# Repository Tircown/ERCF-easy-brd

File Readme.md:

# ERCF EASY BRD

**Be careful not to invert polarity in the screw terminal or it may damage the board and even more.**

**Do not use the servo connector as an input or do it at your own risk.\
Voltage input connected to general I/O pins may cause chip damage if it' higher than 3.3V .**

## BOM
Component | Position
------------ | -------------
Resistor 10K | R1, R2, R3, R4
Capacitor ceramic 0.33uF 25V | C1
Capacitor ceramic 0.1uF 25V | C2
Capacitor 100uF 25V | C3, C4
2P Screw terminal P=5.08 | J5
3P JST-XH male P=2.54 | J1, J2, J3, J4
4P JST-XH male P=2.54 | J6, J7
8P Header socket P=2.54 | *4x for U4 and U3*
2P Header socket P=2.54 | *1x for U4*
5P Header pin P=2.54 | J6
7P Header socket female P=2.54 | *(optionnal) 2x for Seeeduino XIAO*
Seeeduino XIAO or Adafruit QT Py (same footprint & pinout)| U1
Voltage regulator L7805CV | U2
SilentStepStick TMC2209 | U3, U4
Jumper P=2.54 | *2x for J6*
Heatsink for TO-220 | *(recommended) 1x for the L7805CP (1)*

*(1) You will need to bend a fin and remove the pin of the TO-220 heatsink. Make sure the PCB has no bare traces underneath or apply an insolator before (i.e. piece of chattertone).*

## Configure the MCU - Seeeduino XIAO
* Install bossac (version ≥1.8)
```
sudo apt install libreadline-dev libwxgtk3.0-*
git clone https://github.com/shumatech/BOSSA.git
cd BOSSA
make
sudo cp bin/bossac /usr/local/bin
```
* Prepare the firmware
```
cd ~/klipper
make menuconfig
```

```
make clean
make
```
* Flashing the Seeeduino XIAO
Connect the Seeeduino XIAO to your raspberry if it's not already done.
Get the port of the XIAO, i.e. `ls /dev/tty*`, and modify the default `/dev/ttyACM1` in the command line bellow.
Use tweezers or short lines to short the RST pins in the diagram twice. The orange LED lights flicker on and light up. Then send in the next few seconds this command line matching your port.
```
sudo /usr/local/bin/bossac -i -d -p /dev/ttyACM1 -e -w -v -R --offset=0x2000 out/klipper.bin
```

More informations on how to reset for flashing:\
https://wiki.seeedstudio.com/Seeeduino-XIAO/#enter-bootloader-mode

## Klipper configuration
See [ercf_hardware.cfg](config/Seeeduino%20XIAO%20-%20SAMD21G18/ercf_hardware.cfg) for the Seeeduino XIAO (most common solution)
Other microcontrollers configurations are available in config/

## Get the PCB Board
If you want to support my work: https://www.pcbway.com/project/shareproject/ERCF_EASY_BRD.html \
*note: default setting is "HASL lead free" but if it doesn't matter to you, just change this option to get more affordable boards.*

Or just download the Gerber files and upload it to the manufacturer of your choice.

## Dimensions

## More pictures

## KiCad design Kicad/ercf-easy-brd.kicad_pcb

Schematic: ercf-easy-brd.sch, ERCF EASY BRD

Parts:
C1: 0.33uF; C_Disc_D3.0mm_W1.6mm_P2.50mm
C2: 0.1uF; C_Disc_D3.0mm_W1.6mm_P2.50mm
C3, C4: 100uF; CP_Radial_D8.0mm_P3.50mm
H1, H2, H3: MountingHole; MountingHole_3.2mm_M3
J1, J2, J3, J4: Conn_01x03_Male; JST_XH_B3B-XH-A_1x03_P2.50mm_Vertical
J5: Screw_Terminal_01x02; TerminalBlock_bornier-2_P5.08mm_2
J6: Conn_01x05_Male; PinHeader_1x05_P2.54mm_Vertical_2
J7, J8: Conn_01x04_Male; JST_XH_B4B-XH-A_1x04_P2.50mm_Vertical
JP7, JP9: Jumper_NO_Small; SolderJumper-2_P1.3mm_Open_RoundedPad1.0x1.5mm
JP8, JP10: Jumper_NC_Small; SolderJumper-2_P1.3mm_Bridged_RoundedPad1.0x1.5mm
R1, R2, R3, R4: 10k; R_Axial_DIN0207_L6.3mm_D2.5mm_P7.62mm_Horizontal
U1: SeeeduinoXIAO; SeeeduinoXIAO-MODULE14P
U2: L7805; TO-220-3_Vertical
U3, U4: TMC2209_SILENTSTEPSTICK; MODULE_TMC2209_SILENTSTEPSTICK; PARTREV v11

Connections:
+3V3: J2.3, J3.3, J4.3, R3.2, R4.2, U1.12, U3.JP2_7, U4.JP1_7, U4.JP2_7
+5V: C2.1, J1.3, U2.3 (OUT)
ENCODER: J2.1, U1.11
EXTRA: J6.2, U1.9
G-DIR: U1.3, U3.JP1_1
G-EN: R3.1, U1.1, U3.JP1_8
G-STEP: U1.2, U3.JP1_2
GND: C1.2, C2.2, C3.2, C4.2, J1.2, J2.2, J3.2, J4.2, J5.1, R1.2, R2.2, U1.13, U2.2 (GND), U3.JP1_6, U3.JP1_7, U3.JP2_2, U3.JP2_8, U4.JP1_6, U4.JP2_2, U4.JP2_8
unnamed: J3.1, J6.1
unnamed: J4.1, J6.5
unnamed: J6.3, U4.JP4_1
unnamed: J7.1, U3.JP2_5
unnamed: J7.2, U3.JP2_4
unnamed: J7.3, U3.JP2_3
unnamed: J7.4, U3.JP2_6
unnamed: J8.1, U4.JP2_5
unnamed: J8.2, U4.JP2_4
unnamed: J8.3, U4.JP2_3
unnamed: J8.4, U4.JP2_6
unnamed: JP7.1, U3.JP1_4
unnamed: JP8.2, U3.JP1_5
unnamed: JP9.1, U4.JP1_4
unnamed: JP10.2, U4.JP1_5
unnamed: R1.1, U3.JP1_3
unnamed: R2.1, U4.JP1_3
S-DIR: U1.7, U4.JP1_1
S-EN: R4.1, U1.4, U4.JP1_8
S-MIN: J6.4, U1.8
S-STEP: U1.6, U4.JP1_2
SERVO: J1.1, U1.10
UART: JP7.2, JP8.1, JP9.2, JP10.1, U1.5
VDC: C1.1, C3.1, C4.1, J5.2, U2.1 (IN), U3.JP2_1, U4.JP2_1

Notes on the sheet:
DCDC-5V
GEAR STEPPER
SELECTOR STEPPER
ENDSTOPS
MCU
- ENCODER
- SERVO
- EXTRA (TOOLHEAD)
- SELECTOR ENDSTOP
CASE 1 (typical): 1-2 PA7 = Extra Endstop 4-5 PB9 = Selector Endstop CASE 2 : 1-2 PA7 = Extra Endstop 3-4 PB9 = Selector TMC2209 Stallguard CASE 3 : 2-3 PA7 = Selector TMC2209 Stallguard 4-5 PB9 = Selector Endstop
stallguard

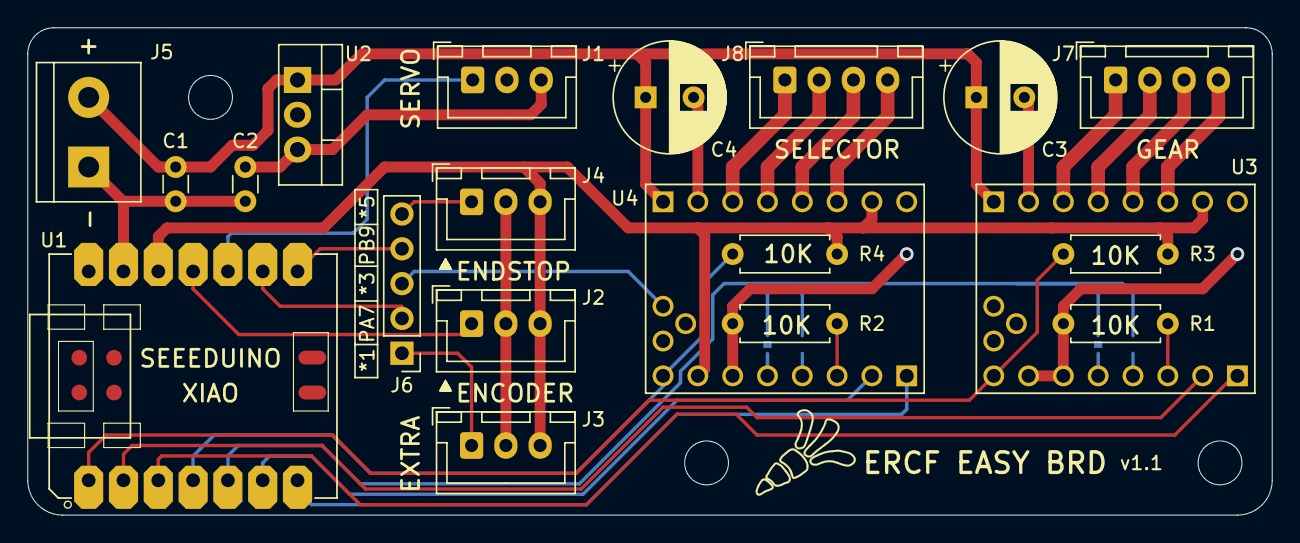
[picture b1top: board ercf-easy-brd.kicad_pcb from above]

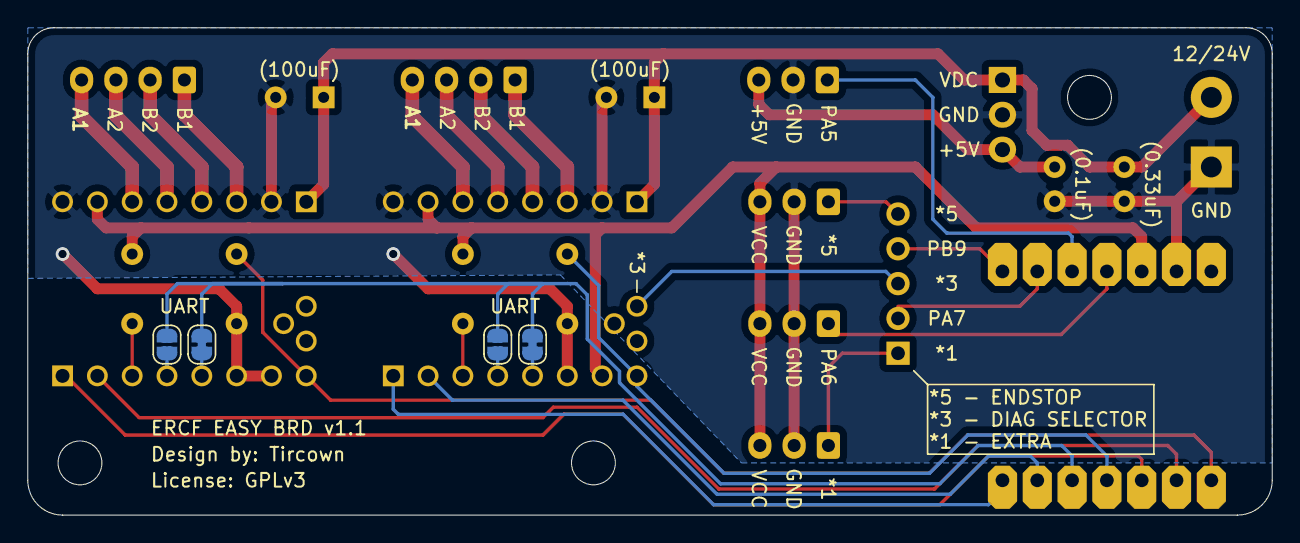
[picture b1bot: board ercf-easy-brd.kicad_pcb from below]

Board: 2 copper layers, 90.8 x 35.6 mm, 27 parts (4 on the bottom side), 32 nets.

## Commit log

2021-05-31 initial
2021-05-31 Fix readme
    Fix readme
2021-05-31 Fix comment on schematic and layout
    Fix comment on schematic and layout
2021-05-31 Add step file
    Add step file
2021-05-31 Fix typo
    Fix typo
2021-05-31 Fix XIAO footprint
    Fix XIAO footprint: one hole smaller
    Rename folder to Kicad
2021-06-01 Complete config sample
    Add the multi mcu section
    Edit pins accordingly to the mcu
    Fix the servo pin
2021-06-01 Open 2nd jumper
    Open the jumper for the second UART pin
2021-06-01 Fix accidently remove the logo
    Fix accidentally remove the logo
    Minor typo in readme
2021-06-17 Fix pin in config
    Fix endstop pin and gear_stepper enable pin in config sample
2021-06-18 PCB v1.1
    PCB v1.1:
    - VCC for endstop, encoder and extra are now 3V3
    - Fix gear stepper ground plane was not connected to GND
    - Improve the tracks width for power and motors
2021-06-24 Rename project
    Rename project from ercf-ez-board to ercf-easy-brd to avoid confusion: it is not a TH3D product.
2021-06-24 Add Adafruit QT Py and general warnings
    Add Adafruit QT Py to the list of mcu since it can be used as a direct replacement.
    Add warnings for the wiring
2021-06-24 Add PCBWay project link
    Add PCBWay project link
2021-06-26 Mod: bracket bottom
    Bottom bracket mod
2021-06-26 Mod: Transport bumper
    Transport bumper mod
2021-06-26 Fix typo
    Fix typo in bottom bracket and transport bumper readmes
2021-06-26 Fix typo
    Fix typo in mods
2021-09-14 Initial files upload
2021-09-14 Replacing images
2021-09-14 images
2021-09-14 re uploading images
2021-09-26 Mod: soldering jig
    Add a mod to help soldering the connectors, XIAO and resistors.
2021-09-26 Fix typo on images paths
    Fix typo on images paths
2021-10-23 - Updated the ercf_hardware.cfg to ercfv1.1 config
2021-10-23 - Typos
2021-11-17 add heatsink in the readme
    Add heatsink in the BOM.
    Add instructions to install the heatsink on the board.
2021-12-08 Update ercf_hardware.cfg
    Remove deprecated settings in ercf_hardware.cfg
    Update the detection_length for the filament_motion_sensor to match the main ERCF repo cfg.
2021-12-08 Update readme: TMC2209
    The easy brd is not compatible with the TMC2208 because of the way it communicates through a single UART wire on different addresses. The TMC2226 should also be compatible according to the datasheet 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
2022-03-28 Add Qt Py SAMD21 pins to the hardware config
    These pins are known good in my config.
2022-03-28 Move and update ercf_hardware.cfg for the XIAO
    Prepare the folders for multiple mcu
    Update ercf_hardware.cfg for the XIAO.
2022-03-28 Create ercf_hardware.cfg for QT Py
    Create ercf_hardware.cfg for QT Py
2022-03-28 Add Qt Py SAMD21 config
2022-03-28 Remove stepper model
2022-04-07 Change links to the config
    Change the links to the config sample.
2022-04-07 Fix link to config sample
    Fix link to config sample
2022-05-01 Recommend L7805CV
    Recommend L7805CV instead of L7805CP.
2022-10-16 Create LICENSE
    Create LICENSE
2023-01-22 add top rail mount mod

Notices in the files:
Kicad/ercf-easy-brd.kicad_pcb:
License: GPLv3
